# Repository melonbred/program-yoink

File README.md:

# Program Yoink!

This PCB is for a 12u main cluster with exploded arrow cluster, macro column and rotary encoder support. Progam Yoink! was a collaborative project with Steve Laroo, P3D Store, and Keybage. 

- Big bar and split bar support
- MX switch support only
- USB Type-C.
- ESD Protection
- RGB lightbar

## Layout

[KLE](http://www.keyboard-layout-editor.com/#/gists/345cd9f384dae3f91f5151f02f8af4df)

 ## PCB

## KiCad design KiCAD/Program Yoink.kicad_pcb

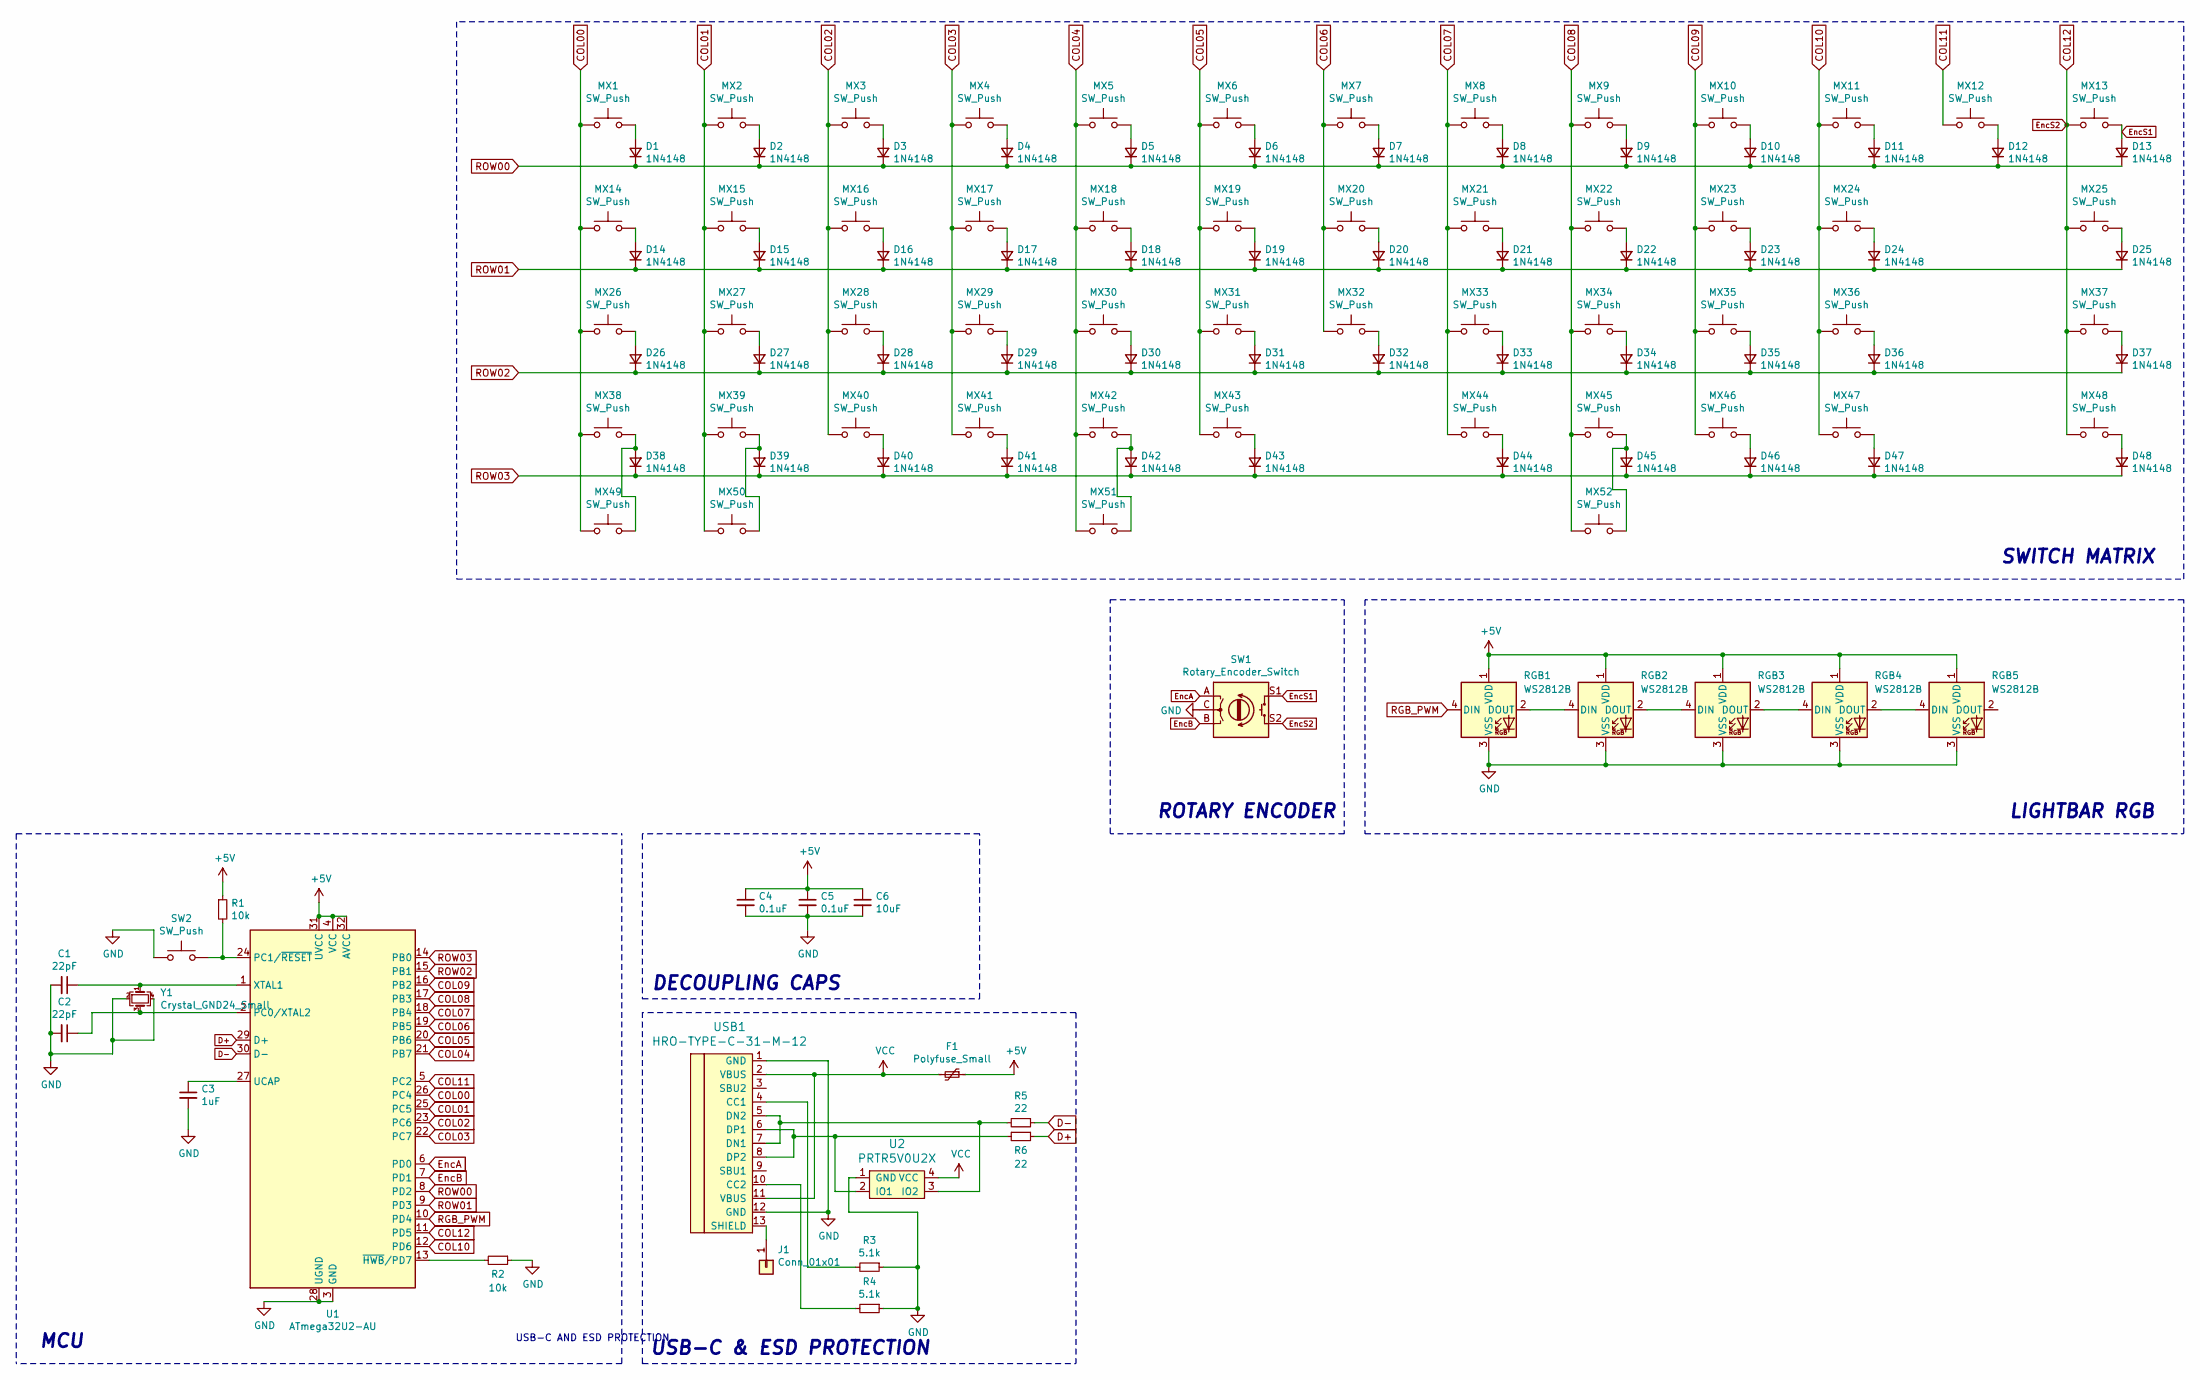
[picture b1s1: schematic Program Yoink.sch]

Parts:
C1, C2: 22pF; C_0805_2012Metric
C3: 1uF; C_0805_2012Metric
C4, C5: 0.1uF; C_0805_2012Metric
C6: 10uF; C_0805_2012Metric
D1, D2, D3, D4, D5, D6, D7, D8, D9, D10, D11, D12, D13, D14, D15, D16, D17, D18, D19, D20, D21, D22, D23, D24, D25, D26, D27, D28, D29, D30, D31, D32, D33, D34, D35, D36, D37, D38, D39, D40, D41, D42, D43, D44, D45, D46, D47, D48: 1N4148; D_SOD-123
F1: Polyfuse_Small; Fuse_1206_3216Metric
J1: Conn_01x01
MX1, MX2, MX3, MX4, MX5, MX6, MX7, MX8, MX9, MX10, MX11, MX12, MX13, MX15, MX16, MX17, MX18, MX19, MX20, MX21, MX22, MX23, MX25, MX27, MX28, MX29, MX30, MX31, MX32, MX33, MX34, MX36, MX37, MX38, MX39, MX40, MX44, MX45, MX46, MX47, MX48: SW_Push; MXOnly-1U-NoLED
MX14, MX35, MX49, MX50, MX52: SW_Push; MXOnly-1.25U-NoLED
MX24, MX26: SW_Push; MXOnly-1.75U-NoLED
MX41: SW_Push; MXOnly-2.75U-ReversedStabilizers-NoLED
MX42: SW_Push; MXOnly-7U-ReversedStabilizers-NoLED
MX43: SW_Push; MXOnly-2.25U-ReversedStabilizers-NoLED
MX51: SW_Push; MXOnly-6.25U-ReversedStabilizers-NoLED
R1, R2: 10k; R_0805_2012Metric
R3, R4: 5.1k; R_0805_2012Metric
R5, R6: 22; R_0805_2012Metric
RGB1, RGB2, RGB3, RGB4, RGB5: WS2812B; LED_WS2812B_PLCC4_5.0x5.0mm_P3.2mm
SW1: Rotary_Encoder_Switch; RotaryEncoder_Alps_EC11E-Switch_Vertical_H20mm
SW2: SW_Push; SKQGADE010
U1: ATmega32U2-AU; TQFP-32_7x7mm_P0.8mm
U2: PRTR5V0U2X; SOT143B
USB1: HRO-TYPE-C-31-M-12; HRO-TYPE-C-31-M-12-Assembly
Y1: Crystal_GND24_Small; Crystal_SMD_3225-4Pin_3.2x2.5mm

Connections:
+5V: C4.1, C5.1, C6.1, F1.1, R1.1, RGB1.1 (VDD), RGB2.1 (VDD), RGB3.1 (VDD), RGB4.1 (VDD), RGB5.1 (VDD), U1.4 (VCC), U1.31 (UVCC), U1.32 (AVCC)
COL00: MX1.1, MX14.1, MX26.1, MX38.1, MX49.1, U1.26 (PC4)
COL01: MX2.1, MX15.1, MX27.1, MX39.1, MX50.1, U1.25 (PC5)
COL02: MX3.1, MX16.1, MX28.1, MX40.1, U1.23 (PC6)
COL03: MX4.1, MX17.1, MX29.1, MX41.1, U1.22 (PC7)
COL04: MX5.1, MX18.1, MX30.1, MX42.1, MX51.1, U1.21 (PB7)
COL05: MX6.1, MX19.1, MX31.1, MX43.1, U1.20 (PB6)
COL06: MX7.1, MX20.1, MX32.1, U1.19 (PB5)
COL07: MX8.1, MX21.1, MX33.1, MX44.1, U1.18 (PB4)
COL08: MX9.1, MX22.1, MX34.1, MX45.1, MX52.1, U1.17 (PB3)
COL09: MX10.1, MX23.1, MX35.1, MX46.1, U1.16 (PB2)
COL10: MX11.1, MX24.1, MX36.1, MX47.1, U1.12 (PD6)
COL11: MX12.1, U1.5 (PC2)
COL12: MX13.1, MX25.1, MX37.1, MX48.1, SW1.S2, U1.11 (PD5)
D+: R6.1, U1.29 (D+)
D-: R5.1, U1.30 (D-)
EncA: SW1.A, U1.6 (PD0)
EncB: SW1.B, U1.7 (PD1)
EncS1: D13.2 (A), MX13.2, SW1.S1
GND: C1.2, C2.2, C3.2, C4.2, C5.2, C6.2, R2.1, R3.1, R4.1, RGB1.3 (VSS), RGB2.3 (VSS), RGB3.3 (VSS), RGB4.3 (VSS), RGB5.3 (VSS), SW1.C, SW2.1, U1.3 (GND), U1.28 (UGND), U2.1 (GND), USB1.1 (GND), USB1.12 (GND), Y1.2, Y1.4
unnamed: C1.1, U1.1 (XTAL1), Y1.1
unnamed: C2.1, U1.2 (PC0/XTAL2), Y1.3
unnamed: C3.1, U1.27 (UCAP)
unnamed: D1.2 (A), MX1.2
unnamed: D2.2 (A), MX2.2
unnamed: D3.2 (A), MX3.2
unnamed: D4.2 (A), MX4.2
unnamed: D5.2 (A), MX5.2
unnamed: D6.2 (A), MX6.2
unnamed: D7.2 (A), MX7.2
unnamed: D8.2 (A), MX8.2
unnamed: D9.2 (A), MX9.2
unnamed: D10.2 (A), MX10.2
unnamed: D11.2 (A), MX11.2
unnamed: D12.2 (A), MX12.2
unnamed: D14.2 (A), MX14.2
unnamed: D15.2 (A), MX15.2
unnamed: D16.2 (A), MX16.2
unnamed: D17.2 (A), MX17.2
unnamed: D18.2 (A), MX18.2
unnamed: D19.2 (A), MX19.2
unnamed: D20.2 (A), MX20.2
unnamed: D21.2 (A), MX21.2
unnamed: D22.2 (A), MX22.2
unnamed: D23.2 (A), MX23.2
unnamed: D24.2 (A), MX24.2
unnamed: D25.2 (A), MX25.2
unnamed: D26.2 (A), MX26.2
unnamed: D27.2 (A), MX27.2
unnamed: D28.2 (A), MX28.2
unnamed: D29.2 (A), MX29.2
unnamed: D30.2 (A), MX30.2
unnamed: D31.2 (A), MX31.2
unnamed: D32.2 (A), MX32.2
unnamed: D33.2 (A), MX33.2
unnamed: D34.2 (A), MX34.2
unnamed: D35.2 (A), MX35.2
unnamed: D36.2 (A), MX36.2
unnamed: D37.2 (A), MX37.2
unnamed: D38.2 (A), MX38.2, MX49.2
unnamed: D39.2 (A), MX39.2, MX50.2
unnamed: D40.2 (A), MX40.2
unnamed: D41.2 (A), MX41.2
unnamed: D42.2 (A), MX42.2, MX51.2
unnamed: D43.2 (A), MX43.2
unnamed: D44.2 (A), MX44.2
unnamed: D45.2 (A), MX45.2, MX52.2
unnamed: D46.2 (A), MX46.2
unnamed: D47.2 (A), MX47.2
unnamed: D48.2 (A), MX48.2
unnamed: J1.1, USB1.13 (SHIELD)
unnamed: R1.2, SW2.2, U1.24 (PC1/~RESET)
unnamed: R2.2, U1.13 (~HWB~/PD7)
unnamed: R3.2, USB1.4 (CC1)
unnamed: R4.2, USB1.10 (CC2)
unnamed: R5.2, U2.3 (IO2), USB1.5 (DN2), USB1.7 (DN1)
unnamed: R6.2, U2.2 (IO1), USB1.6 (DP1), USB1.8 (DP2)
unnamed: RGB1.2 (DOUT), RGB2.4 (DIN)
unnamed: RGB2.2 (DOUT), RGB3.4 (DIN)
unnamed: RGB3.2 (DOUT), RGB4.4 (DIN)
unnamed: RGB4.2 (DOUT), RGB5.4 (DIN)
RGB_PWM: RGB1.4 (DIN), U1.10 (PD4)
ROW00: D1.1 (K), D2.1 (K), D3.1 (K), D4.1 (K), D5.1 (K), D6.1 (K), D7.1 (K), D8.1 (K), D9.1 (K), D10.1 (K), D11.1 (K), D12.1 (K), D13.1 (K), U1.8 (PD2)
ROW01: D14.1 (K), D15.1 (K), D16.1 (K), D17.1 (K), D18.1 (K), D19.1 (K), D20.1 (K), D21.1 (K), D22.1 (K), D23.1 (K), D24.1 (K), D25.1 (K), U1.9 (PD3)
ROW02: D26.1 (K), D27.1 (K), D28.1 (K), D29.1 (K), D30.1 (K), D31.1 (K), D32.1 (K), D33.1 (K), D34.1 (K), D35.1 (K), D36.1 (K), D37.1 (K), U1.15 (PB1)
ROW03: D38.1 (K), D39.1 (K), D40.1 (K), D41.1 (K), D42.1 (K), D43.1 (K), D44.1 (K), D45.1 (K), D46.1 (K), D47.1 (K), D48.1 (K), U1.14 (PB0)
VCC: F1.2, U2.4 (VCC), USB1.2 (VBUS), USB1.11 (VBUS)

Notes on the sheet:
SWITCH MATRIX
LIGHTBAR RGB
MCU
DECOUPLING CAPS
USB-C AND ESD PROTECTION
USB-C & ESD PROTECTION
ROTARY ENCODER

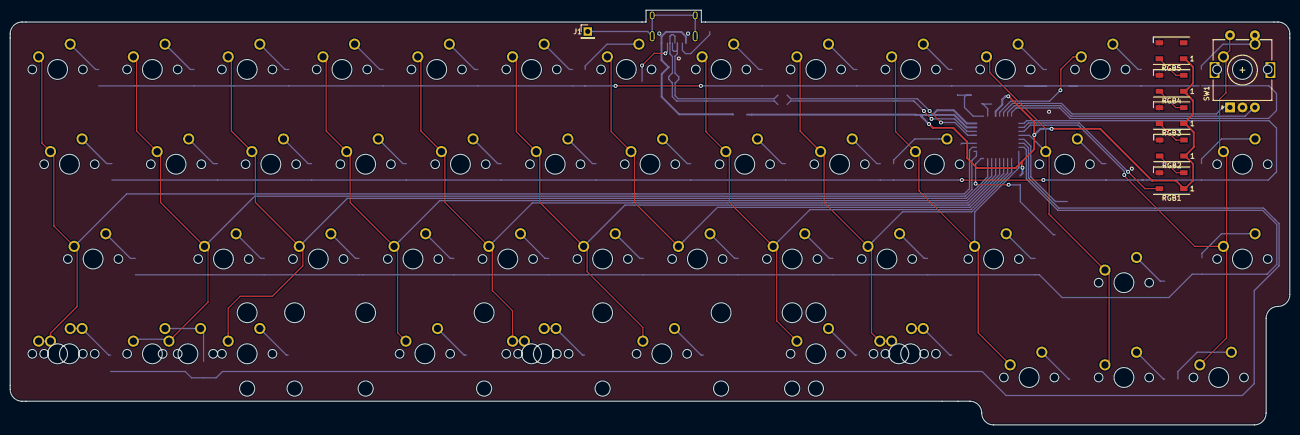
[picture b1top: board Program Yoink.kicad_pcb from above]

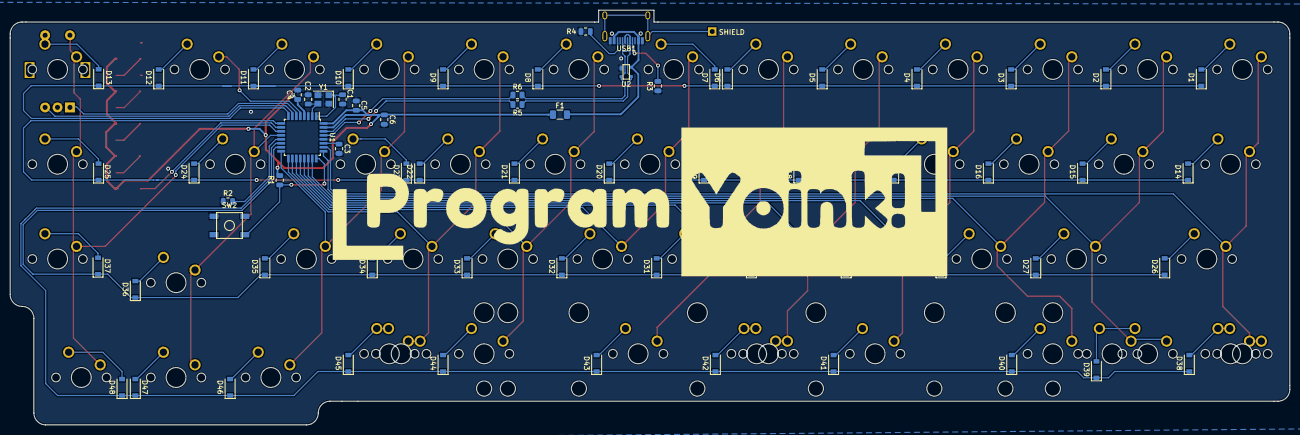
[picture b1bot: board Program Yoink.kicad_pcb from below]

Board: 2 copper layers, 257.2 x 83.3 mm, 125 parts (66 on the bottom side), 87 nets.

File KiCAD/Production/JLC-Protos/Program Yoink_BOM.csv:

"Designator";"Quantity";"Value";"Footprint";"LCSC Part#"
"R2,R1";2;"10k";"0805";"C365230"
"USB1";1;"HRO-TYPE-C-31-M-12";"HRO-TYPE-C-31-M-12-HandSoldering";"C283541"
"U2";1;"PRTR5V0U2X";"SOT-143";"C316030"
"R4,R3";2;"5.1k";"0805";"C328405"
"F1";1;"Polyfuse_Small";1206;"C70076"
"Y1";1;"Crystal_GND24_Small";3225;"C156247"
"SW2";1;"SW_Push";;"C116647"
"C6";1;"10uF";"0805";"C1713"
"C5,C4";2;"0.1uF";"0805";"C1760"
"C3";1;"1uF";"0805";"C50683"
"C2,C1";2;"22pF";"0805";"C165459"
"U1";1;"ATmega32U2-AU";"TQFP-32_7x7mm_P0.8mm";
"D46,D48,D47,D45,D44,D43,D42,D41,D40,D39,D38,D37,D36,D35,D34,D33,D32,D31,D30,D29,D28,D27,D26,D25,D24,D23,D22,D21,D20,D19,D18,D17,D16,D15,D14,D13,D12,D11,D10,D9,D8,D7,D6,D5,D4,D3,D2,D1";48;"1N4148";"SOD-123";"C466653"

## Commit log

2020-10-03 Completed v0.1 PCB
2020-10-03 Updated Symbol lib path
2020-10-16 Fixed LED gnd
2020-10-24 Updated traces
2020-11-04 Updated PCB
    Added resistors to data lines
2020-11-06 Added data resistors
2020-11-07 Prepared production files
2020-12-04 Updated PCB
2021-05-16 Production Files
2021-05-16 Added images
2021-05-17 Organization
